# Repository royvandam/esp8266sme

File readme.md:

# Prometheus Exporter for Smartmeter with P1 serial port

**To be extended**

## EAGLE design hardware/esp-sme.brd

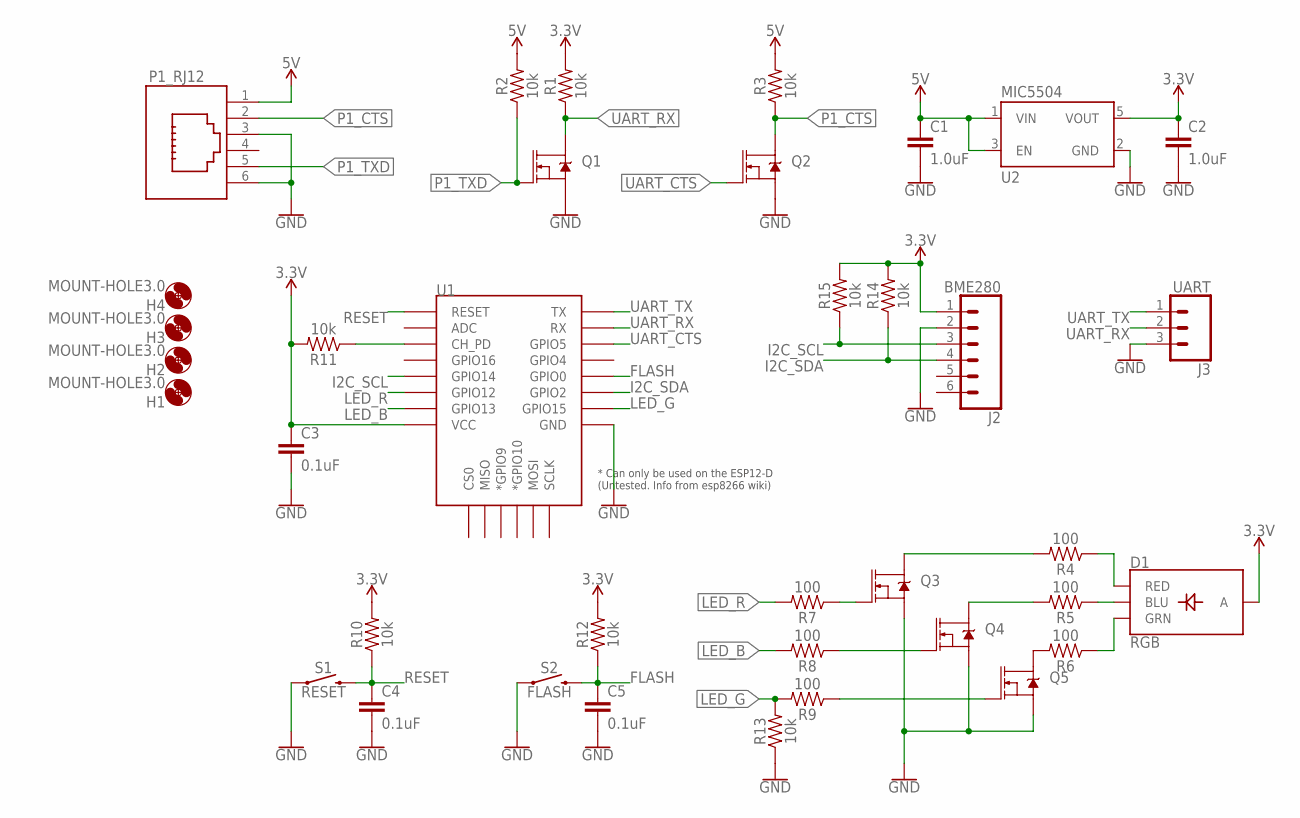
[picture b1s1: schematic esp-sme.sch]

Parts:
C1, C2: 1.0uF; 0603
C3, C4, C5: 0.1uF; 0603
D1: RGB; P-LCC-4-3
H1, H2, H3, H4: MOUNT-HOLE3.0; 3,0
J2: BME280; 1X06
J3: UART; 1X03
P1_RJ12: 615006143621
Q1, Q2, Q3, Q4, Q5: MOSFET-NCH-AO3404A; SOT23-3
R1, R2, R3, R10, R11, R12, R13, R14, R15: 10k; 0603
R4, R5, R6, R7, R8, R9: 100; 0603
S1: RESET; TACTILE_SWITCH_SMD_4.6X2.8MM
S2: FLASH; TACTILE_SWITCH_SMD_4.6X2.8MM
U1: ESP12ESMD; ESP12E-SMD
U2: MIC5504; SOT23-5

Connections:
3.3V: C2.1, C3.1, D1.4 (A), J2.1, R1.2, R10.2, R11.2, R12.2, R14.2, R15.2, U1.VCC, U2.5 (VOUT)
5V: C1.1, P1_RJ12.1 (6), R2.2, R3.2, U2.1 (VIN), U2.3 (EN)
FLASH: C5.1, R12.1, S2.3 (2), S2.4 (2), U1.GPIO0
GND: C1.2, C2.2, C3.2, C4.2, C5.2, J2.2, J3.3, P1_RJ12.3 (4), P1_RJ12.6 (1), Q1.2 (S), Q2.2 (S), Q3.2 (S), Q4.2 (S), Q5.2 (S), R13.1, S1.1, S1.2 (1), S2.1, S2.2 (1), U1.GND, U2.2 (GND)
I2C_SCL: J2.3, R15.1, U1.GPIO14
I2C_SDA: J2.4, R14.1, U1.GPIO2
LED_B: R8.2, U1.GPIO13
LED_G: R9.2, R13.2, U1.GPIO15
LED_R: R7.2, U1.GPIO12
unnamed: D1.3 (BLU), R5.1
unnamed: D1.1 (RED), R4.1
unnamed: D1.2 (GRN), R6.1
unnamed: Q5.3 (D), R6.2
unnamed: Q4.3 (D), R5.2
unnamed: Q3.3 (D), R4.2
unnamed: Q5.1 (G), R9.1
unnamed: Q4.1 (G), R8.1
unnamed: Q3.1 (G), R7.1
unnamed: R11.1, U1.CH_PD
P1_CTS: P1_RJ12.2 (5), Q2.3 (D), R3.1
P1_TXD: P1_RJ12.5 (2), Q1.1 (G), R2.1
RESET: C4.1, R10.1, S1.3 (2), S1.4 (2), U1.RESET
UART_CTS: Q2.1 (G), U1.GPIO5
UART_RX: J3.2, Q1.3 (D), R1.1, U1.RXD0 (RX)
UART_TX: J3.1, U1.TXD0 (TX)

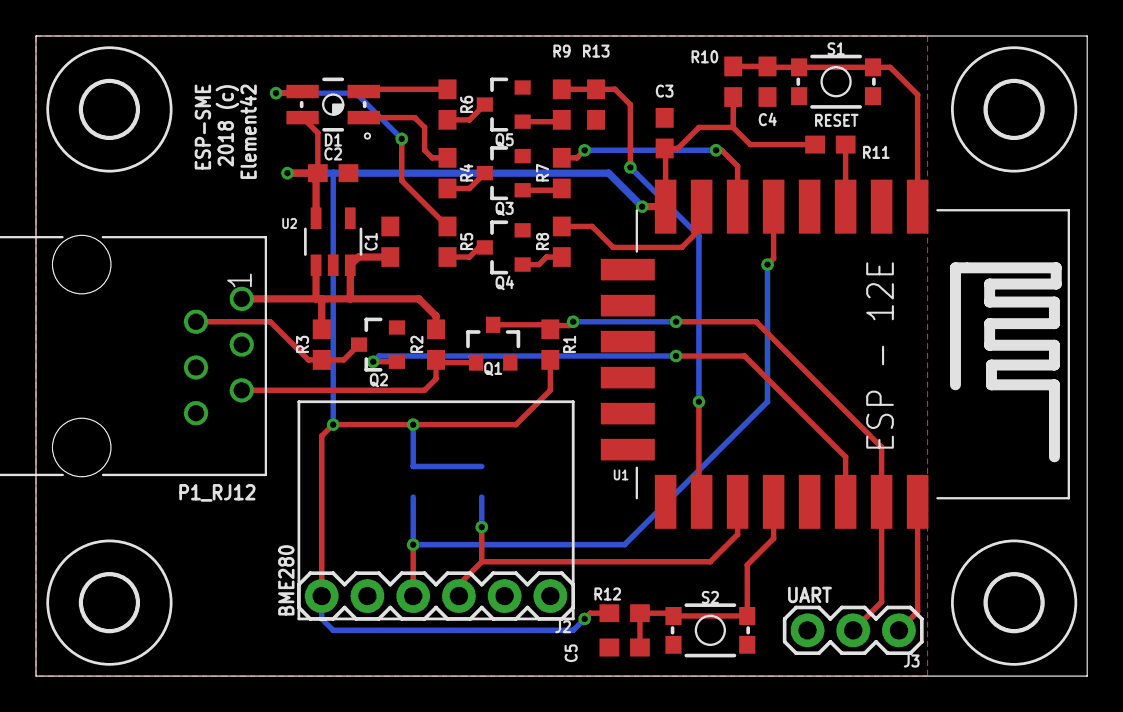
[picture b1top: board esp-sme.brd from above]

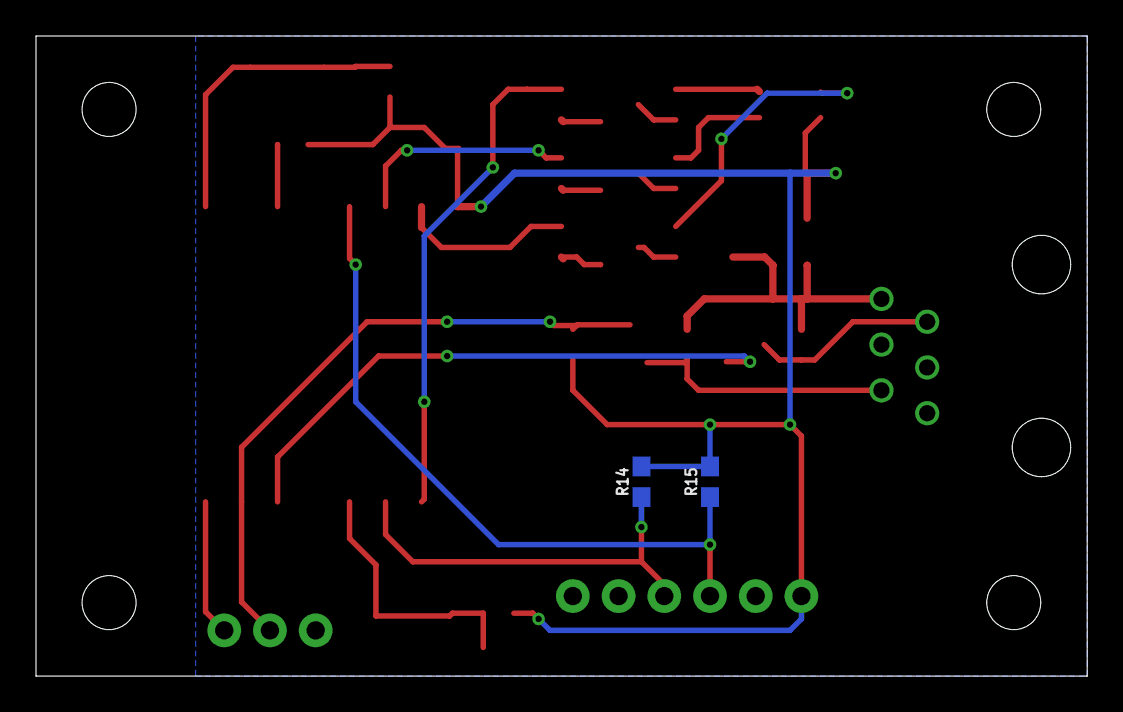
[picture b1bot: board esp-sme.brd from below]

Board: 2 copper layers, 58.4 x 35.6 mm, 37 parts (2 on the bottom side), 25 nets.

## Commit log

2018-03-18 Initial version
2018-03-19 Added boot-pin configuration
2018-04-10 Initial software demo
2018-04-10 Demo implementation based on asyncio
2018-04-10 Removed obsolete files
2018-04-10 Added license file and stub readme
2018-04-10 Replaced transistor for n-channel mosfet
2018-04-11 Fixed metrics encoding format, causing scrapes to fail

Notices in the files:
parts and their libraries:
InputOutputIO: Copyright: Würth Elektronik
SparkFun-PowerSymbols: Licensing: Creative Commons ShareAlike 4.0 International - https://creativecommons.org/licenses/by-sa/4.0
